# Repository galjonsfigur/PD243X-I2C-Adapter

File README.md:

# PD243X I²C Display Adapter Board

This repository contains KiCad design files, schematics and gerber files for a simple adapter board that allows to use old PD2435, PD2436 and PD2437 dot-matrix displays with most microcontrollers using I²C protocol instead of pin-consuming  parallel interface. They can be used as neat little displays for any project that requires some kind of simple and old-looking display.

## Photo (more in `images` folder)

## Details
PD245x displays are small four-digit alphanumeric dot-matrix displays. They use 8-bit data bus, 3-bit address line and additional signals to receive data from microcontroller. Because parallel interface requires many I/O pins to work, a simple I²C adapter board was designed. It uses 2 PCF8574T ICs to control all required pins of the display.

## Compatibility

This adapter board was designed with PD2435 in mind but it's working also with other color variants. According to the datasheet Also PD323X and PD443X displays can be used but probably they won't fit on this PCB as nicely as PD243X. 

## Bill of materials

- *1x*: PD243X display
- *1x*: 4 pin single row right angled header with 2.54mm pin spacing
- *2x*: PFC8574 I²C expander in SOIC-16 package
- *1x*: 100nF capacitor in 0805 SMD package
- *2x*: 4.7k ohm resisttor in 0805 SMD package
- *2x*: 470 ohm resisttor in 0805 SMD package
- *1x*: Green LED in 1206 SMD package
- *1x*: Red LED in 1206 SMD package

## License

[Solderpad Hardware Licence Version 2.0](LICENSE.md)

## Author
[Galion](galion$AT$sdf.org)

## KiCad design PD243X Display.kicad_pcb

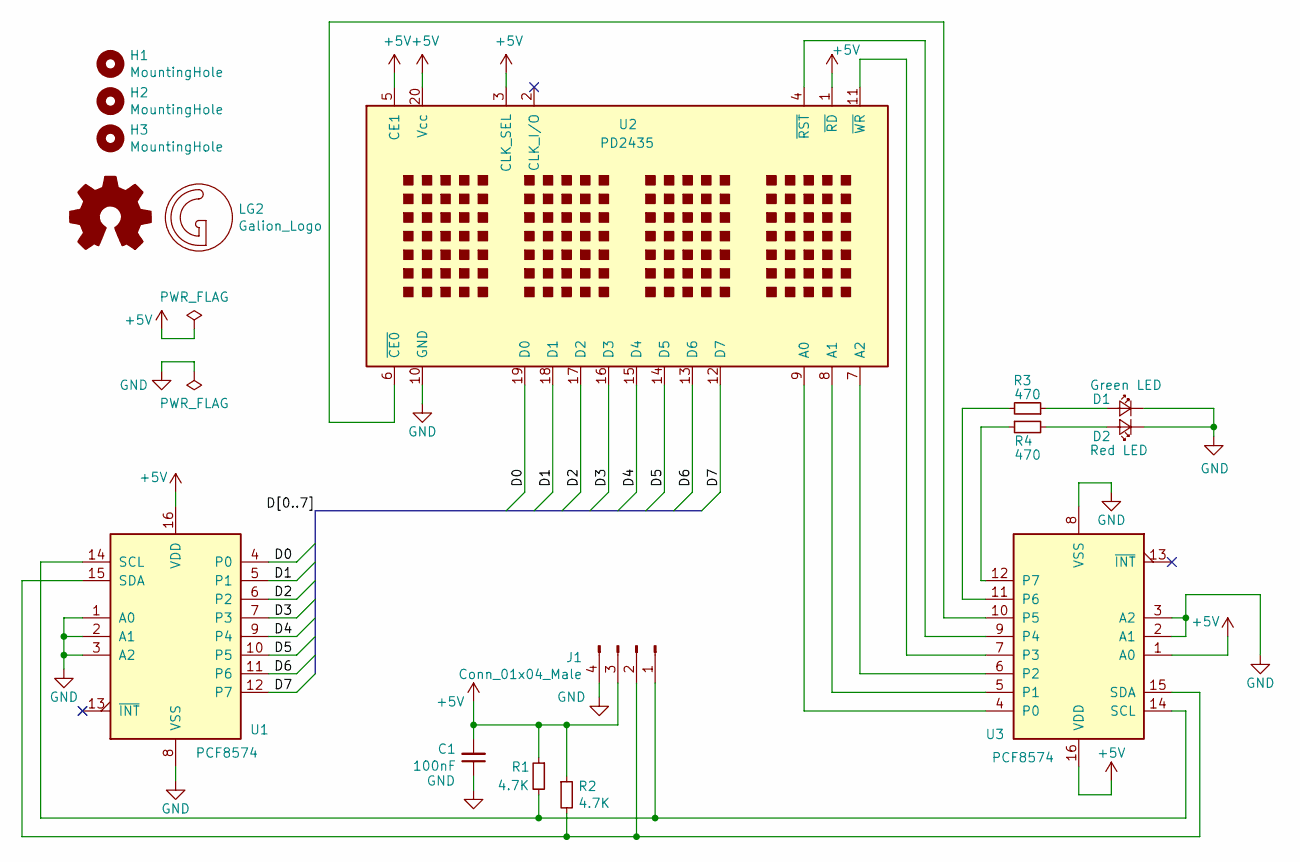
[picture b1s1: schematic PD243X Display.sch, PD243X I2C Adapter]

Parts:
C1: 100nF; C_0805_2012Metric_Pad1.15x1.40mm_HandSolder
D1: Green LED; LED_1206_3216Metric_Pad1.42x1.75mm_HandSolder
D2: Red LED; LED_1206_3216Metric_Pad1.42x1.75mm_HandSolder
H1, H2, H3: MountingHole; MountingHole_2.2mm_M2_Pad_Via
J1: Conn_01x04_Male; PinHeader_1x04_P2.54mm_Horizontal_cut
LG1: Logo_Open_Hardware_Small; OSHW-Symbol_5.7x6mm_SilkScreen
LG2: Galion_Logo; Galion_Logo_Small
R1, R2: 4.7K; R_0805_2012Metric_Pad1.15x1.40mm_HandSolder
R3, R4: 470; R_0805_2012Metric_Pad1.15x1.40mm_HandSolder
U1, U3: PCF8574; SOIC-16W_7.5x10.3mm_P1.27mm
U2: PD2435; DIP-20_W15.24mm_LongPads

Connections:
+5V: C1.2, J1.3, R1.1, R2.1, U1.16 (VDD), U2.1 (~RD), U2.3 (CLK_SEL), U2.5 (CE1), U2.20 (Vcc), U3.1 (A0), U3.16 (VDD)
/D0: U1.4 (P0), U2.19 (D0)
/D1: U1.5 (P1), U2.18 (D1)
/D2: U1.6 (P2), U2.17 (D2)
/D3: U1.7 (P3), U2.16 (D3)
/D4: U1.9 (P4), U2.15 (D4)
/D5: U1.10 (P5), U2.14 (D5)
/D6: U1.11 (P6), U2.13 (D6)
/D7: U1.12 (P7), U2.12 (D7)
GND: C1.1, D1.1 (K), D2.1 (K), J1.4, U1.1 (A0), U1.2 (A1), U1.3 (A2), U1.8 (VSS), U2.10 (GND), U3.2 (A1), U3.3 (A2), U3.8 (VSS)
unnamed: D1.2 (A), R3.1
unnamed: D2.2 (A), R4.2
unnamed: J1.1, R1.2, U1.14 (SCL), U3.14 (SCL)
unnamed: J1.2, R2.2, U1.15 (SDA), U3.15 (SDA)
unnamed: R3.2, U3.11 (P6)
unnamed: R4.1, U3.12 (P7)
unnamed: U2.4 (~RST), U3.9 (P4)
unnamed: U2.6 (~CE0), U3.10 (P5)
unnamed: U2.7 (A2), U3.6 (P2)
unnamed: U2.8 (A1), U3.5 (P1)
unnamed: U2.9 (A0), U3.4 (P0)
unnamed: U2.11 (~WR), U3.7 (P3)

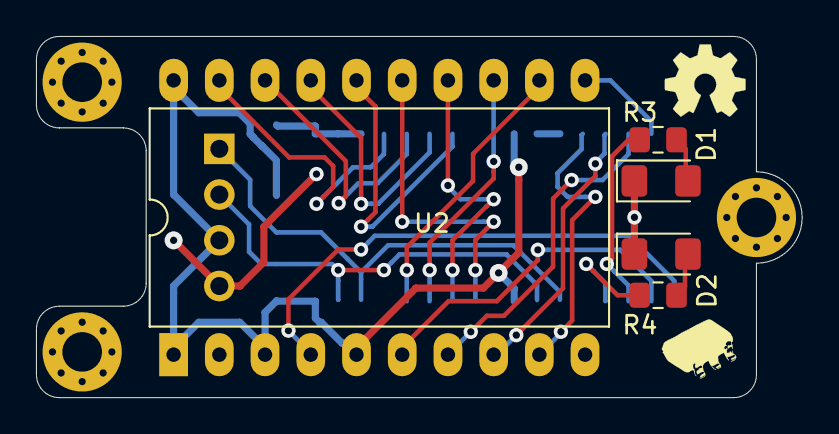
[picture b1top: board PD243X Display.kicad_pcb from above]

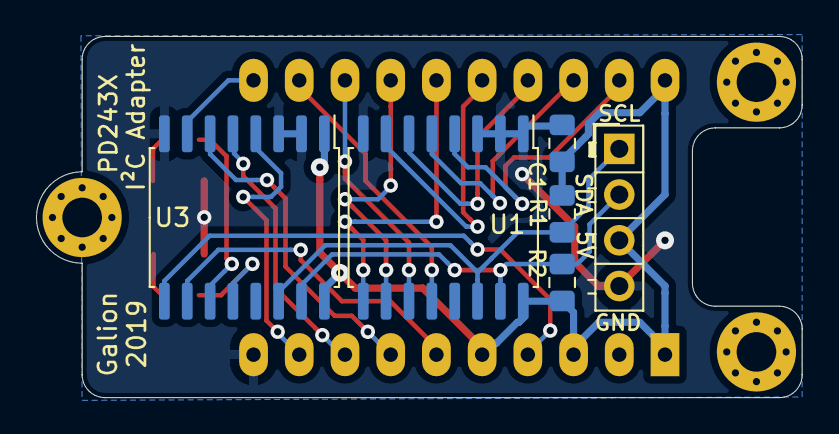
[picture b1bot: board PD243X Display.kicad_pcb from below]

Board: 2 copper layers, 42.5 x 20.1 mm, 16 parts (6 on the bottom side), 22 nets.
